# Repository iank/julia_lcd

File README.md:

# julia_lcd

TFT LCD panel, capacitive touch controller, Xilinx Cyclone IV FPGA, SDR SDRAM

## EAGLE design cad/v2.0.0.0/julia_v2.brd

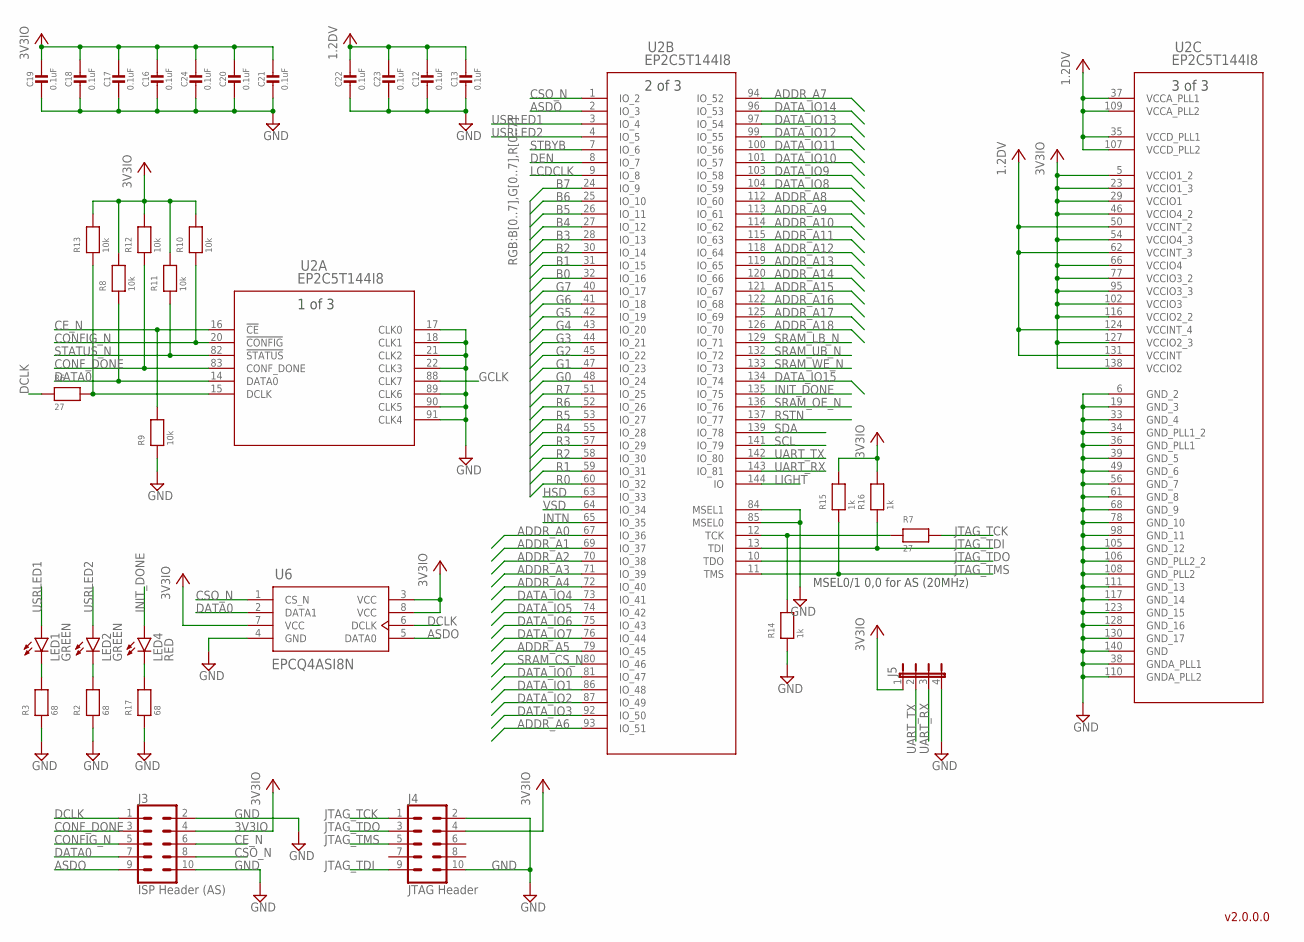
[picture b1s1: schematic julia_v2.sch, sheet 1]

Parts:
C12, C13, C16, C17, C18, C19, C20, C21, C22, C23, C24: 0.1uF; 0805; MPN 0805ZD104KAT2A
J3: ISP Header (AS); 2X5-SHROUDED; MPN SBH11-PBPC-D05-ST-BK
J4: JTAG Header; 2X5-SHROUDED; MPN SBH11-PBPC-D05-ST-BK
J5: JP4E; JP4
LED1, LED2: GREEN; CHIPLED_0805; MPN ML-LXT0805IW-TR
LED4: RED; CHIPLED_0805; MPN SML-LXT0805IW-TR
R2, R3, R17: 68; 0805; MPN RC0805FR-0768RL
R6, R7: 27; 0805; MPN RC0805JR-0727RL
R8, R9, R10, R11, R12, R13: 10k; 0805; MPN RC0805FR-0710KL
R14, R15, R16: 1k; 0805; MPN RC0805FR-071KL
U2: EP2C5T144I8; 144-TQFP_ALR; MPN EP2C5T144I8
U6: EPCQ4ASI8N; 8SOIC

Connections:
1.2DV: C12.1, C13.1, C22.1, C23.1, U2.35 (VCCD_PLL1), U2.37 (VCCA_PLL1), U2.50 (VCCINT_2), U2.62 (VCCINT_3), U2.107 (VCCD_PLL2), U2.109 (VCCA_PLL2), U2.124 (VCCINT_4), U2.131 (VCCINT); also elsewhere on the board
3V3IO: C16.1, C17.1, C18.1, C19.1, C20.1, C21.1, C24.1, J3.4, J4.4, J5.1, R8.2, R10.2, R11.2, R12.2, R13.2, R15.2, R16.2, U2.5 (VCCIO1_2), U2.23 (VCCIO1_3), U2.29 (VCCIO1), U2.46 (VCCIO4_2), U2.54 (VCCIO4_3), U2.66 (VCCIO4), U2.77 (VCCIO3_2), U2.95 (VCCIO3_3), U2.102 (VCCIO3), U2.116 (VCCIO2_2), U2.127 (VCCIO2_3), U2.138 (VCCIO2), U6.3 (VCC), U6.7 (VCC), U6.8 (VCC); also elsewhere on the board
ADDR_A0: U2.67 (IO_36); also elsewhere on the board
ADDR_A1: U2.69 (IO_37); also elsewhere on the board
ADDR_A2: U2.70 (IO_38); also elsewhere on the board
ADDR_A3: U2.71 (IO_39); also elsewhere on the board
ADDR_A4: U2.72 (IO_40); also elsewhere on the board
ADDR_A5: U2.79 (IO_45); also elsewhere on the board
ADDR_A6: U2.93 (IO_51); also elsewhere on the board
ADDR_A7: U2.94 (IO_52); also elsewhere on the board
ADDR_A8: U2.112 (IO_60); also elsewhere on the board
ADDR_A9: U2.113 (IO_61); also elsewhere on the board
ADDR_A10: U2.114 (IO_62); also elsewhere on the board
ADDR_A11: U2.115 (IO_63); also elsewhere on the board
ADDR_A12: U2.118 (IO_64); also elsewhere on the board
ADDR_A13: U2.119 (IO_65); also elsewhere on the board
ADDR_A14: U2.120 (IO_66); also elsewhere on the board
ADDR_A15: U2.121 (IO_67); also elsewhere on the board
ADDR_A16: U2.122 (IO_68); also elsewhere on the board
ADDR_A17: U2.125 (IO_69); also elsewhere on the board
ADDR_A18: U2.126 (IO_70); also elsewhere on the board
ASDO: J3.9, U2.2 (IO_3), U6.5 (DATA0)
B0: U2.32 (IO_16); also elsewhere on the board
B1: U2.31 (IO_15); also elsewhere on the board
B2: U2.30 (IO_14); also elsewhere on the board
B3: U2.28 (IO_13); also elsewhere on the board
B4: U2.27 (IO_12); also elsewhere on the board
B5: U2.26 (IO_11); also elsewhere on the board
B6: U2.25 (IO_10); also elsewhere on the board
B7: U2.24 (IO_9); also elsewhere on the board
CE_N: J3.6, R9.2, U2.16 (!CE)
CONFIG_N: J3.5, R10.1, U2.20 (!CONFIG)
CONF_DONE: J3.3, R12.1, U2.83 (CONF_DONE)
CSO_N: J3.8, U2.1 (IO_2), U6.1 (CS_N)
DATA0: J3.7, R8.1, U2.14 (DATA0), U6.2 (DATA1)
DATA_IO0: U2.81 (IO_47); also elsewhere on the board
DATA_IO1: U2.86 (IO_48); also elsewhere on the board
DATA_IO2: U2.87 (IO_49); also elsewhere on the board
DATA_IO3: U2.92 (IO_50); also elsewhere on the board
DATA_IO4: U2.73 (IO_41); also elsewhere on the board
DATA_IO5: U2.74 (IO_42); also elsewhere on the board
DATA_IO6: U2.75 (IO_43); also elsewhere on the board
DATA_IO7: U2.76 (IO_44); also elsewhere on the board
DATA_IO8: U2.104 (IO_59); also elsewhere on the board
DATA_IO9: U2.103 (IO_58); also elsewhere on the board
DATA_IO10: U2.101 (IO_57); also elsewhere on the board
DATA_IO11: U2.100 (IO_56); also elsewhere on the board
DATA_IO12: U2.99 (IO_55); also elsewhere on the board
DATA_IO13: U2.97 (IO_54); also elsewhere on the board
DATA_IO14: U2.96 (IO_53); also elsewhere on the board
DATA_IO15: U2.134 (IO_74); also elsewhere on the board
DCLK: J3.1, R6.1, U6.6 (DCLK)
DEN: U2.8 (IO_7); also elsewhere on the board
G0: U2.48 (IO_24); also elsewhere on the board
G1: U2.47 (IO_23); also elsewhere on the board
G2: U2.45 (IO_22); also elsewhere on the board
G3: U2.44 (IO_21); also elsewhere on the board
G4: U2.43 (IO_20); also elsewhere on the board
G5: U2.42 (IO_19); also elsewhere on the board
G6: U2.41 (IO_18); also elsewhere on the board
G7: U2.40 (IO_17); also elsewhere on the board
GCLK: U2.88 (CLK7); also elsewhere on the board
GND: C12.2, C13.2, C16.2, C17.2, C18.2, C19.2, C20.2, C21.2, C22.2, C23.2, C24.2, J3.2, J3.10, J4.2, J4.10, J5.4, R2.1, R3.1, R9.1, R14.1, R17.1, U2.6 (GND_2), U2.17 (CLK0), U2.18 (CLK1), U2.19 (GND_3), U2.21 (CLK2), U2.22 (CLK3), U2.33 (GND_4), U2.34 (GND_PLL1_2), U2.36 (GND_PLL1), U2.38 (GNDA_PLL1), U2.39 (GND_5), U2.49 (GND_6), U2.56 (GND_7), U2.61 (GND_8), U2.68 (GND_9), U2.78 (GND_10), U2.84 (MSEL1), U2.85 (MSEL0), U2.89 (CLK6), U2.90 (CLK5), U2.91 (CLK4), U2.98 (GND_11), U2.105 (GND_12), U2.106 (GND_PLL2_2), U2.108 (GND_PLL2), U2.110 (GNDA_PLL2), U2.111 (GND_13), U2.117 (GND_14), U2.123 (GND_15), U2.128 (GND_16), U2.130 (GND_17), U2.140 (GND), U6.4 (GND); also elsewhere on the board
HSD: U2.63 (IO_33); also elsewhere on the board
INIT_DONE: LED4.A, U2.135 (IO_75)
INTN: U2.65 (IO_35); also elsewhere on the board
JTAG_TCK: J4.1, R7.2
JTAG_TDI: J4.9, R16.1, U2.13 (TDI)
JTAG_TDO: J4.3, U2.10 (TDO)
JTAG_TMS: J4.5, R15.1, U2.11 (TMS)
LCDCLK: U2.9 (IO_8); also elsewhere on the board
LIGHT: U2.144 (IO); also elsewhere on the board
unnamed: R6.2, R13.1, U2.15 (DCLK)
unnamed: LED1.C, R3.2
unnamed: R7.1, R14.2, U2.12 (TCK)
unnamed: LED4.C, R17.2
unnamed: LED2.C, R2.2
R0: U2.60 (IO_32); also elsewhere on the board
R1: U2.59 (IO_31); also elsewhere on the board
R2: U2.58 (IO_30); also elsewhere on the board
R3: U2.57 (IO_29); also elsewhere on the board
R4: U2.55 (IO_28); also elsewhere on the board
R5: U2.53 (IO_27); also elsewhere on the board
R6: U2.52 (IO_26); also elsewhere on the board
R7: U2.51 (IO_25); also elsewhere on the board
RSTN: U2.137 (IO_77); also elsewhere on the board
SCL: U2.141 (IO_79); also elsewhere on the board
SDA: U2.139 (IO_78); also elsewhere on the board
SRAM_CS_N: U2.80 (IO_46); also elsewhere on the board
SRAM_LB_N: U2.129 (IO_71); also elsewhere on the board
SRAM_OE_N: U2.136 (IO_76); also elsewhere on the board
SRAM_UB_N: U2.132 (IO_72); also elsewhere on the board
SRAM_WE_N: U2.133 (IO_73); also elsewhere on the board
STATUS_N: R11.1, U2.82 (!STATUS); also elsewhere on the board
STBYB: U2.7 (IO_6); also elsewhere on the board
UART_RX: J5.3, U2.143 (IO_81)
UART_TX: J5.2, U2.142 (IO_80)
USRLED1: LED1.A, U2.3 (IO_4)
USRLED2: LED2.A, U2.4 (IO_5)
VSD: U2.64 (IO_34); also elsewhere on the board

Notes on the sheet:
MSEL0/1 0,0 for AS (20MHz)
v2.0.0.0

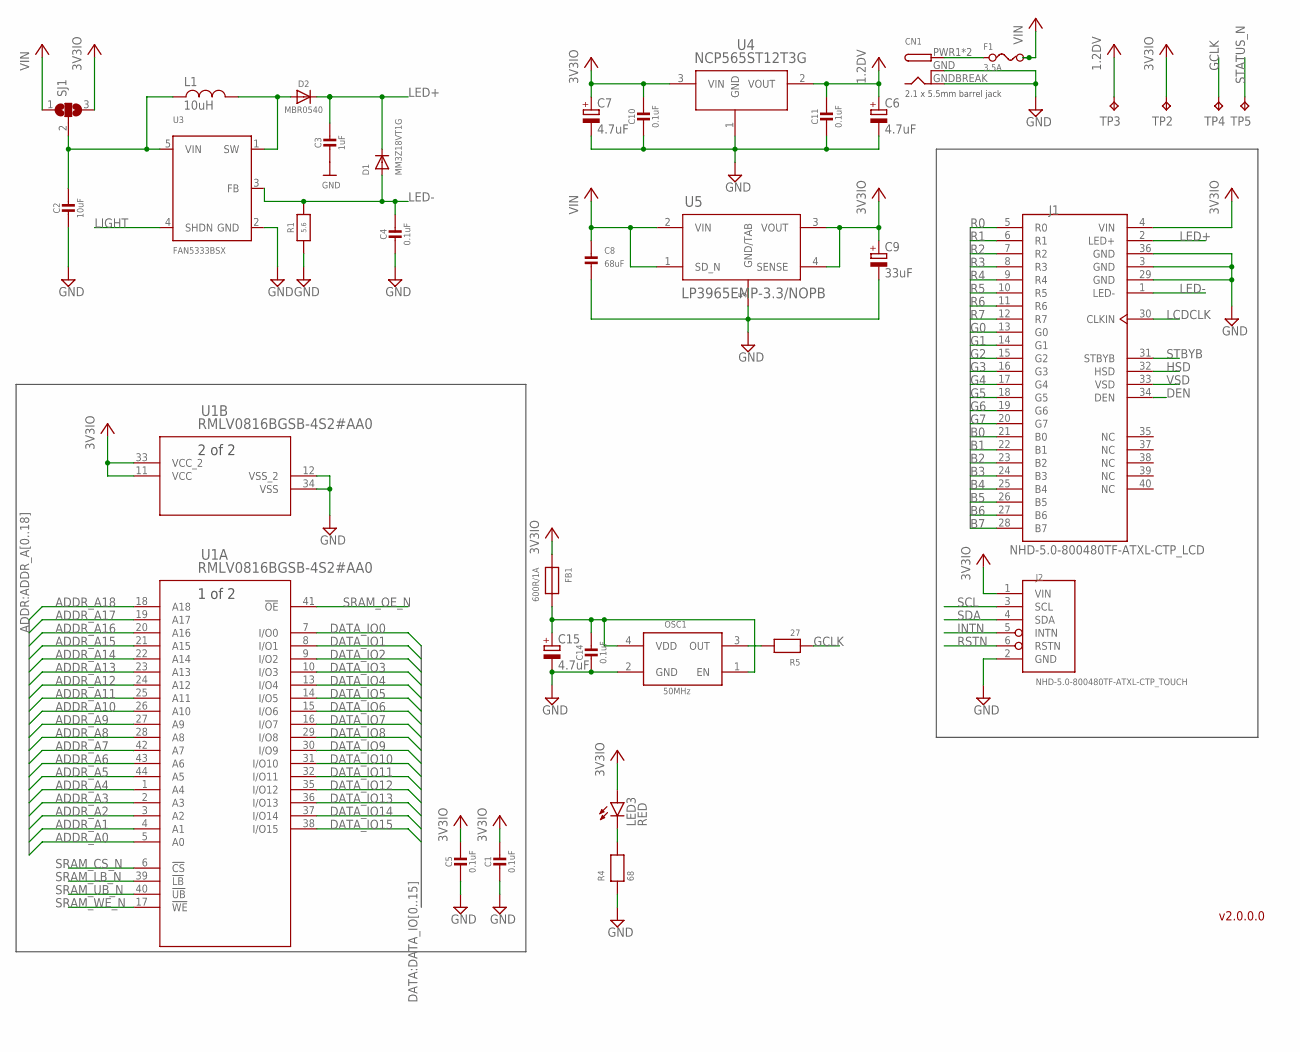
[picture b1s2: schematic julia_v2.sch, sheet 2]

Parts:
C1, C4, C5, C10, C11, C14: 0.1uF; 0805; MPN 0805ZD104KAT2A
C2: 10uF; 0805; MPN CL21A106KPFNNNG
C3: 1uF; 0805; MPN CL21A105KACLNNC
C6, C7, C15: 4.7uF; CPOL0805; MPN F920J475MPA
C8: 68uF; 1206; MPN C3216X5R1A686M160AC
C9: 33uF; CPOL0805; MPN TLJP336M010R3500
CN1: DCBARRELSMT; DCJACK_2MM_SMT
D1: MM3Z18VT1G; SOD-323; MPN MM3Z18VT1G
D2: MBR0540; SOD-123; MPN MBR0540
F1: 3.5A; 1206
FB1: 600R/1A; 0603; MPN MI0603J601R-10
J1: NHD-5.0-800480TF-ATXL-CTP_LCD; 54132-4097; MPN 54104-4031
J2: NHD-5.0-800480TF-ATXL-CTP_TOUCH; 52271-0679; MPN 52271-0679
L1: 10uH; SPM10040T-100M-HZ
LED3: RED; CHIPLED_0805; MPN SML-LXT0805IW-TR
OSC1: 50MHz; CRYSTALASV
R1: 5.6; 0805; MPN RC0805FR-075R6L
R4: 68; 0805; MPN RC0805FR-0768RL
R5: 27; 0805; MPN RC0805JR-0727RL
SJ1: SJ2WW; SJ_2W
TP2, TP3, TP4, TP5: TPB1,27; B1,27
U1: RMLV0816BGSB-4S2#AA0; PTSB0044GG-A_REN
U3: FAN5333BSX; SOT23-5@1; MPN FAN5333BSX
U4: NCP565ST12T3G; SOT223-3_ONS
U5: LP3965EMP-3.3/NOPB; NDC0005A

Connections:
1.2DV: C6.1 (+), C11.1, TP3.TP, U4.2 (VOUT); also elsewhere on the board
3V3IO: C1.1, C5.1, C7.1 (+), C9.1 (+), C10.1, FB1.1, J1.4 (VIN), J2.1 (VIN), LED3.A, SJ1.3, TP2.TP, U1.11 (VCC), U1.33 (VCC_2), U4.3 (VIN), U5.3 (VOUT), U5.4 (SENSE); also elsewhere on the board
ADDR_A0: U1.5 (A0); also elsewhere on the board
ADDR_A1: U1.4 (A1); also elsewhere on the board
ADDR_A2: U1.3 (A2); also elsewhere on the board
ADDR_A3: U1.2 (A3); also elsewhere on the board
ADDR_A4: U1.1 (A4); also elsewhere on the board
ADDR_A5: U1.44 (A5); also elsewhere on the board
ADDR_A6: U1.43 (A6); also elsewhere on the board
ADDR_A7: U1.42 (A7); also elsewhere on the board
ADDR_A8: U1.28 (A8); also elsewhere on the board
ADDR_A9: U1.27 (A9); also elsewhere on the board
ADDR_A10: U1.26 (A10); also elsewhere on the board
ADDR_A11: U1.25 (A11); also elsewhere on the board
ADDR_A12: U1.24 (A12); also elsewhere on the board
ADDR_A13: U1.23 (A13); also elsewhere on the board
ADDR_A14: U1.22 (A14); also elsewhere on the board
ADDR_A15: U1.21 (A15); also elsewhere on the board
ADDR_A16: U1.20 (A16); also elsewhere on the board
ADDR_A17: U1.19 (A17); also elsewhere on the board
ADDR_A18: U1.18 (A18); also elsewhere on the board
B0: J1.21 (B0); also elsewhere on the board
B1: J1.22 (B1); also elsewhere on the board
B2: J1.23 (B2); also elsewhere on the board
B3: J1.24 (B3); also elsewhere on the board
B4: J1.25 (B4); also elsewhere on the board
B5: J1.26 (B5); also elsewhere on the board
B6: J1.27 (B6); also elsewhere on the board
B7: J1.28 (B7); also elsewhere on the board
DATA_IO0: U1.7 (I/O0); also elsewhere on the board
DATA_IO1: U1.8 (I/O1); also elsewhere on the board
DATA_IO2: U1.9 (I/O2); also elsewhere on the board
DATA_IO3: U1.10 (I/O3); also elsewhere on the board
DATA_IO4: U1.13 (I/O4); also elsewhere on the board
DATA_IO5: U1.14 (I/O5); also elsewhere on the board
DATA_IO6: U1.15 (I/O6); also elsewhere on the board
DATA_IO7: U1.16 (I/O7); also elsewhere on the board
DATA_IO8: U1.29 (I/O8); also elsewhere on the board
DATA_IO9: U1.30 (I/O9); also elsewhere on the board
DATA_IO10: U1.31 (I/O10); also elsewhere on the board
DATA_IO11: U1.32 (I/O11); also elsewhere on the board
DATA_IO12: U1.35 (I/O12); also elsewhere on the board
DATA_IO13: U1.36 (I/O13); also elsewhere on the board
DATA_IO14: U1.37 (I/O14); also elsewhere on the board
DATA_IO15: U1.38 (I/O15); also elsewhere on the board
DEN: J1.34 (DEN); also elsewhere on the board
F_SW: D2.A, L1.1, U3.1 (SW)
F_VIN: C2.1, L1.2, SJ1.2, U3.5 (VIN)
G0: J1.13 (G0); also elsewhere on the board
G1: J1.14 (G1); also elsewhere on the board
G2: J1.15 (G2); also elsewhere on the board
G3: J1.16 (G3); also elsewhere on the board
G4: J1.17 (G4); also elsewhere on the board
G5: J1.18 (G5); also elsewhere on the board
G6: J1.19 (G6); also elsewhere on the board
G7: J1.20 (G7); also elsewhere on the board
GCLK: R5.1, TP4.TP; also elsewhere on the board
GND: C1.2, C2.2, C3.2, C4.2, C5.2, C6.2 (-), C7.2 (-), C8.2, C9.2 (-), C10.2, C11.2, C14.2, C15.2 (-), CN1.GND, CN1.GNDBREAK, J1.3 (GND), J1.29 (GND), J1.36 (GND), J2.2 (GND), OSC1.2 (GND), R1.1, R4.1, U1.12 (VSS_2), U1.34 (VSS), U3.2 (GND), U4.1 (GND), U5.5 (GND/TAB); also elsewhere on the board
HSD: J1.32 (HSD); also elsewhere on the board
INTN: J2.5 (INTN); also elsewhere on the board
LCDCLK: J1.30 (CLKIN); also elsewhere on the board
LED+: C3.1, D1.1 (C), D2.C, J1.2 (LED+)
LED-: C4.1, D1.2 (A), J1.1 (LED-), R1.2, U3.3 (FB)
LIGHT: U3.4 (SHDN); also elsewhere on the board
unnamed: CN1.PWR1 (PWR), CN1.PWR2 (PWR), F1.1
unnamed: LED3.C, R4.2
OSC_V: C14.1, C15.1 (+), FB1.2, OSC1.1 (EN), OSC1.4 (VDD)
R0: J1.5 (R0); also elsewhere on the board
R1: J1.6 (R1); also elsewhere on the board
R2: J1.7 (R2); also elsewhere on the board
R3: J1.8 (R3); also elsewhere on the board
R4: J1.9 (R4); also elsewhere on the board
R5: J1.10 (R5); also elsewhere on the board
R6: J1.11 (R6); also elsewhere on the board
R7: J1.12 (R7); also elsewhere on the board
RSTN: J2.6 (RSTN); also elsewhere on the board
SCL: J2.3 (SCL); also elsewhere on the board
SDA: J2.4 (SDA); also elsewhere on the board
SRAM_CS_N: U1.6 (!CS); also elsewhere on the board
SRAM_LB_N: U1.39 (!LB); also elsewhere on the board
SRAM_OE_N: U1.41 (!OE); also elsewhere on the board
SRAM_UB_N: U1.40 (!UB); also elsewhere on the board
SRAM_WE_N: U1.17 (!WE); also elsewhere on the board
STATUS_N: TP5.TP; also elsewhere on the board
STBYB: J1.31 (STBYB); also elsewhere on the board
VIN: C8.1, F1.2, SJ1.1, U5.1 (SD_N), U5.2 (VIN)
VSD: J1.33 (VSD); also elsewhere on the board
_GCLK: OSC1.3 (OUT), R5.2

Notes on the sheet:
2.1 x 5.5mm barrel jack
v2.0.0.0

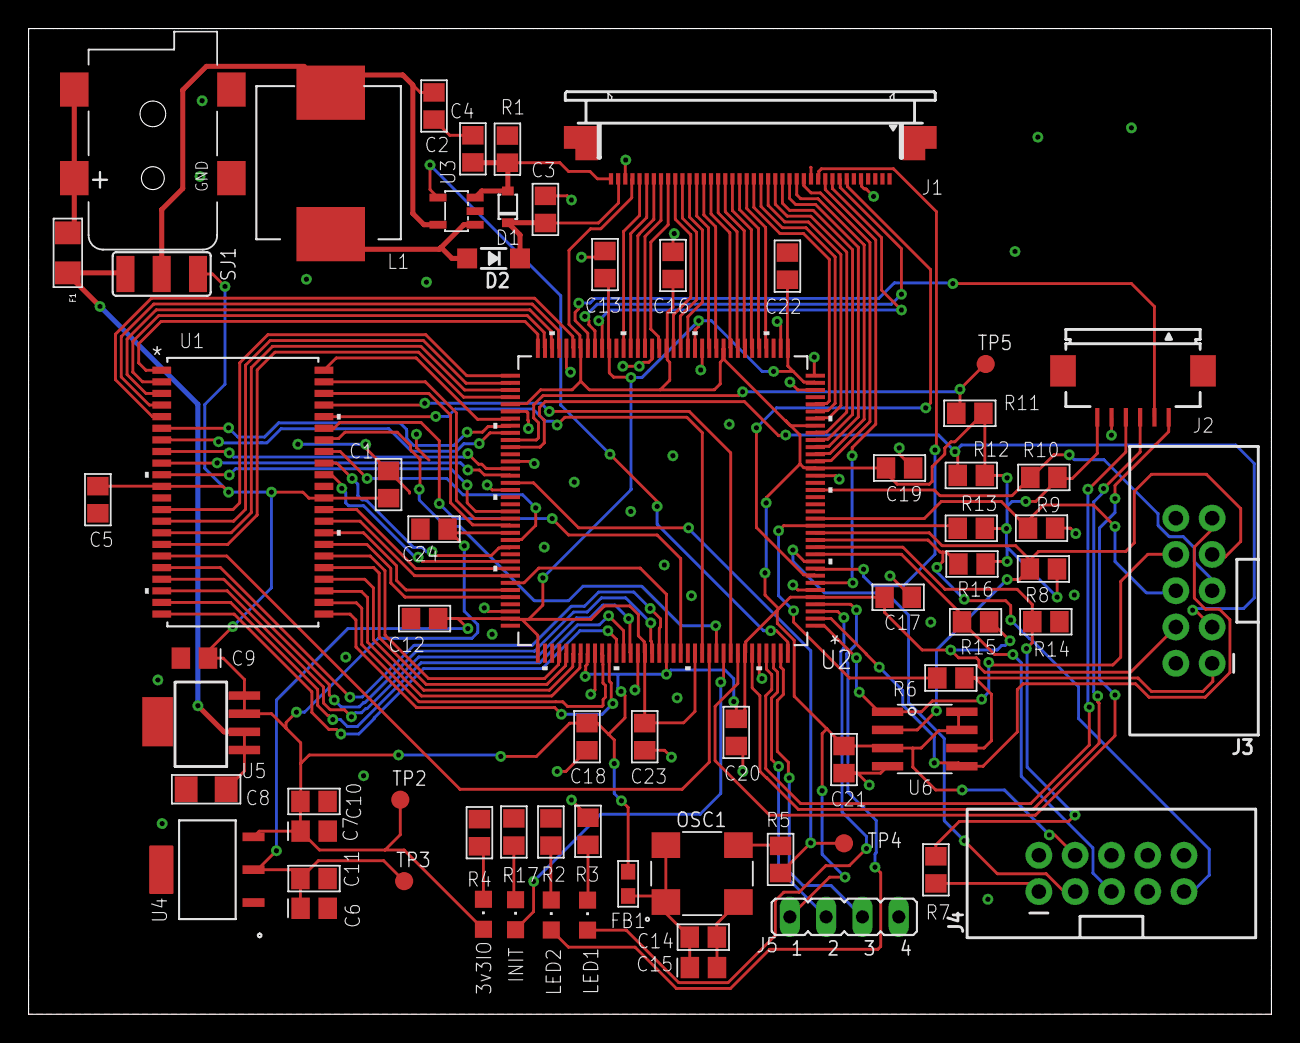
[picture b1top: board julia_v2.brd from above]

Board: 2 copper layers, 87.0 x 69.0 mm, 68 parts (0 on the bottom side), 109 nets.

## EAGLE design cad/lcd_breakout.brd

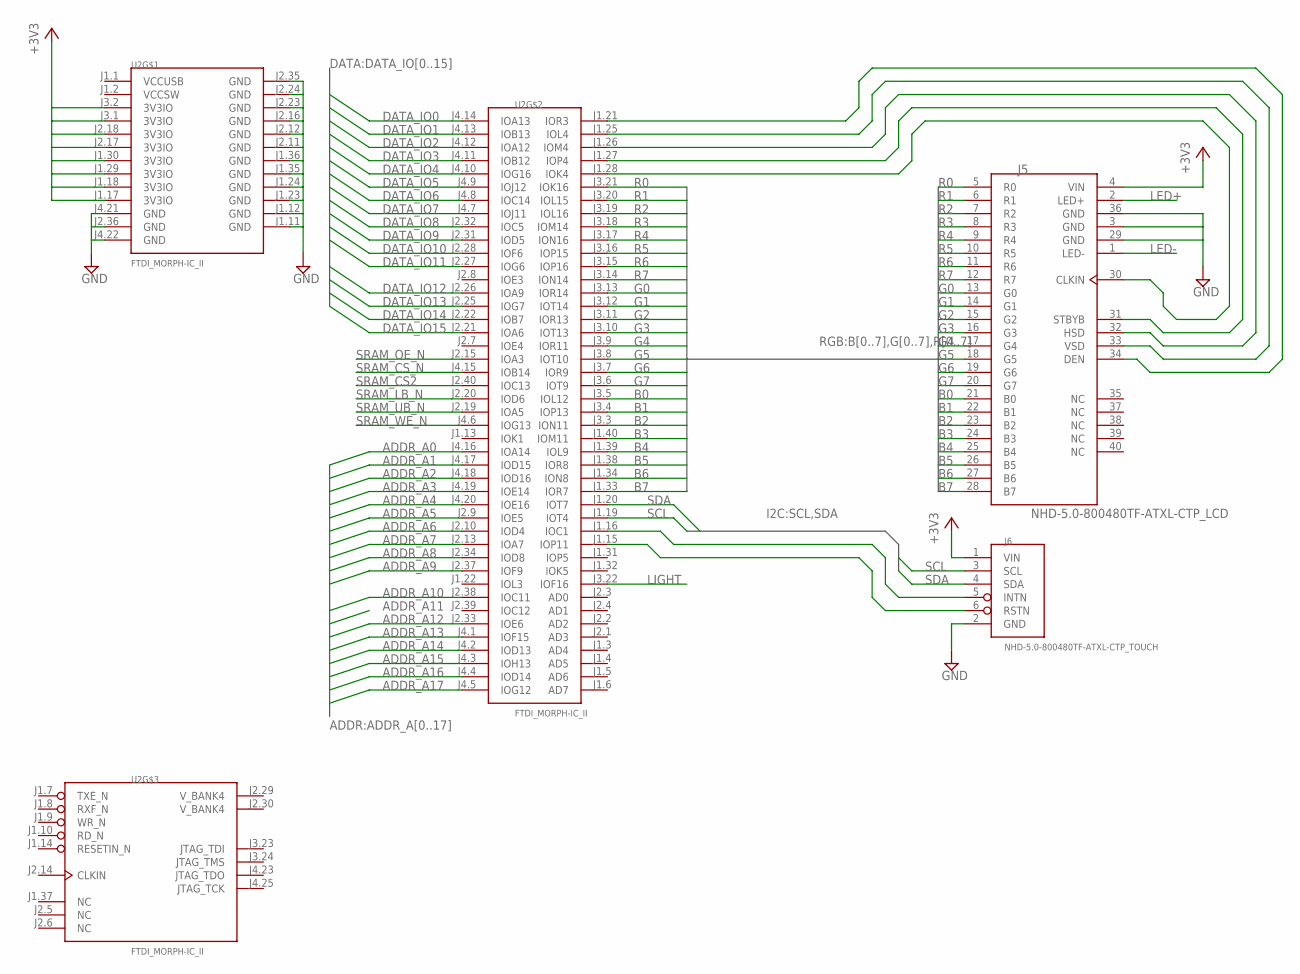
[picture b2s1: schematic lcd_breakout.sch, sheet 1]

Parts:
J5: NHD-5.0-800480TF-ATXL-CTP_LCD; 54132-4097; MPN 54104-4031
J6: NHD-5.0-800480TF-ATXL-CTP_TOUCH; 52271-0679; MPN 52271-0679
U2: FTDI_MORPH-IC_II; MORPH-IC-II; MPN 2x NPPC202KFMS-RC, 2x NPPC122KFMS-RC

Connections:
+3V3: J5.4 (VIN), J6.1 (VIN), U2.J1.17 (3V3IO), U2.J1.18 (3V3IO), U2.J1.29 (3V3IO), U2.J1.30 (3V3IO), U2.J2.17 (3V3IO), U2.J2.18 (3V3IO), U2.J3.1 (3V3IO), U2.J3.2 (3V3IO); also elsewhere on the board
ADDR_A0: U2.J4.16 (IOA14); also elsewhere on the board
ADDR_A1: U2.J4.17 (IOD15); also elsewhere on the board
ADDR_A2: U2.J4.18 (IOD16); also elsewhere on the board
ADDR_A3: U2.J4.19 (IOE14); also elsewhere on the board
ADDR_A4: U2.J4.20 (IOE16); also elsewhere on the board
ADDR_A5: U2.J2.9 (IOE5); also elsewhere on the board
ADDR_A6: U2.J2.10 (IOD4); also elsewhere on the board
ADDR_A7: U2.J2.13 (IOA7); also elsewhere on the board
ADDR_A8: U2.J2.34 (IOD8); also elsewhere on the board
ADDR_A9: U2.J2.37 (IOF9); also elsewhere on the board
ADDR_A10: U2.J2.38 (IOC11); also elsewhere on the board
ADDR_A12: U2.J2.33 (IOE6); also elsewhere on the board
ADDR_A13: U2.J4.1 (IOF15); also elsewhere on the board
ADDR_A14: U2.J4.2 (IOD13); also elsewhere on the board
ADDR_A15: U2.J4.3 (IOH13); also elsewhere on the board
ADDR_A16: U2.J4.4 (IOD14); also elsewhere on the board
ADDR_A17: U2.J4.5 (IOG12); also elsewhere on the board
B0: J5.21 (B0), U2.J3.5 (IOL12)
B1: J5.22 (B1), U2.J3.4 (IOP13)
B2: J5.23 (B2), U2.J3.3 (ION11)
B3: J5.24 (B3), U2.J1.40 (IOM11)
B4: J5.25 (B4), U2.J1.39 (IOL9)
B5: J5.26 (B5), U2.J1.38 (IOR8)
B6: J5.27 (B6), U2.J1.34 (ION8)
B7: J5.28 (B7), U2.J1.33 (IOR7)
CLKIN: J5.30 (CLKIN), U2.J1.28 (IOK4)
DATA_IO0: U2.J4.14 (IOA13); also elsewhere on the board
DATA_IO1: U2.J4.13 (IOB13); also elsewhere on the board
DATA_IO2: U2.J4.12 (IOA12); also elsewhere on the board
DATA_IO3: U2.J4.11 (IOB12); also elsewhere on the board
DATA_IO4: U2.J4.10 (IOG16); also elsewhere on the board
DATA_IO5: U2.J4.9 (IOJ12); also elsewhere on the board
DATA_IO6: U2.J4.8 (IOC14); also elsewhere on the board
DATA_IO7: U2.J4.7 (IOJ11); also elsewhere on the board
DATA_IO8: U2.J2.32 (IOC5); also elsewhere on the board
DATA_IO9: U2.J2.31 (IOD5); also elsewhere on the board
DATA_IO10: U2.J2.28 (IOF6); also elsewhere on the board
DATA_IO11: U2.J2.27 (IOG6); also elsewhere on the board
DATA_IO12: U2.J2.26 (IOA9); also elsewhere on the board
DATA_IO13: U2.J2.25 (IOG7); also elsewhere on the board
DATA_IO14: U2.J2.22 (IOB7); also elsewhere on the board
DATA_IO15: U2.J2.21 (IOA6); also elsewhere on the board
DEN: J5.34 (DEN), U2.J1.21 (IOR3)
G0: J5.13 (G0), U2.J3.13 (IOR14)
G1: J5.14 (G1), U2.J3.12 (IOT14)
G2: J5.15 (G2), U2.J3.11 (IOR13)
G3: J5.16 (G3), U2.J3.10 (IOT13)
G4: J5.17 (G4), U2.J3.9 (IOR11)
G5: J5.18 (G5), U2.J3.8 (IOT10)
G6: J5.19 (G6), U2.J3.7 (IOR9)
G7: J5.20 (G7), U2.J3.6 (IOT9)
GND: J5.3 (GND), J5.29 (GND), J5.36 (GND), J6.2 (GND), U2.J1.11 (GND), U2.J1.12 (GND), U2.J1.23 (GND), U2.J1.24 (GND), U2.J1.35 (GND), U2.J1.36 (GND), U2.J2.11 (GND), U2.J2.12 (GND), U2.J2.16 (GND), U2.J2.23 (GND), U2.J2.24 (GND), U2.J2.35 (GND), U2.J2.36 (GND), U2.J4.21 (GND), U2.J4.22 (GND); also elsewhere on the board
HSD: J5.32 (HSD), U2.J1.26 (IOM4)
INTN: J6.5 (INTN), U2.J1.16 (IOC1)
LED+: J5.2 (LED+); also elsewhere on the board
LED-: J5.1 (LED-); also elsewhere on the board
LIGHT: U2.J3.22 (IOF16); also elsewhere on the board
R0: J5.5 (R0), U2.J3.21 (IOK16)
R1: J5.6 (R1), U2.J3.20 (IOL15)
R2: J5.7 (R2), U2.J3.19 (IOL16)
R3: J5.8 (R3), U2.J3.18 (IOM14)
R4: J5.9 (R4), U2.J3.17 (ION16)
R5: J5.10 (R5), U2.J3.16 (IOP15)
R6: J5.11 (R6), U2.J3.15 (IOP16)
R7: J5.12 (R7), U2.J3.14 (ION14)
RSTN: J6.6 (RSTN), U2.J1.15 (IOP11)
SCL: J6.3 (SCL), U2.J1.19 (IOT4)
SDA: J6.4 (SDA), U2.J1.20 (IOT7)
SRAM_CS2: U2.J2.40 (IOC13); also elsewhere on the board
SRAM_CS_N: U2.J4.15 (IOB14); also elsewhere on the board
SRAM_LB_N: U2.J2.20 (IOD6); also elsewhere on the board
SRAM_OE_N: U2.J2.15 (IOA3); also elsewhere on the board
SRAM_UB_N: U2.J2.19 (IOA5); also elsewhere on the board
SRAM_WE_N: U2.J4.6 (IOG13); also elsewhere on the board
STBYB: J5.31 (STBYB), U2.J1.27 (IOP4)
VCCSW: U2.J1.2 (VCCSW)
VCCUSB: U2.J1.1 (VCCUSB)
VSD: J5.33 (VSD), U2.J1.25 (IOL4)

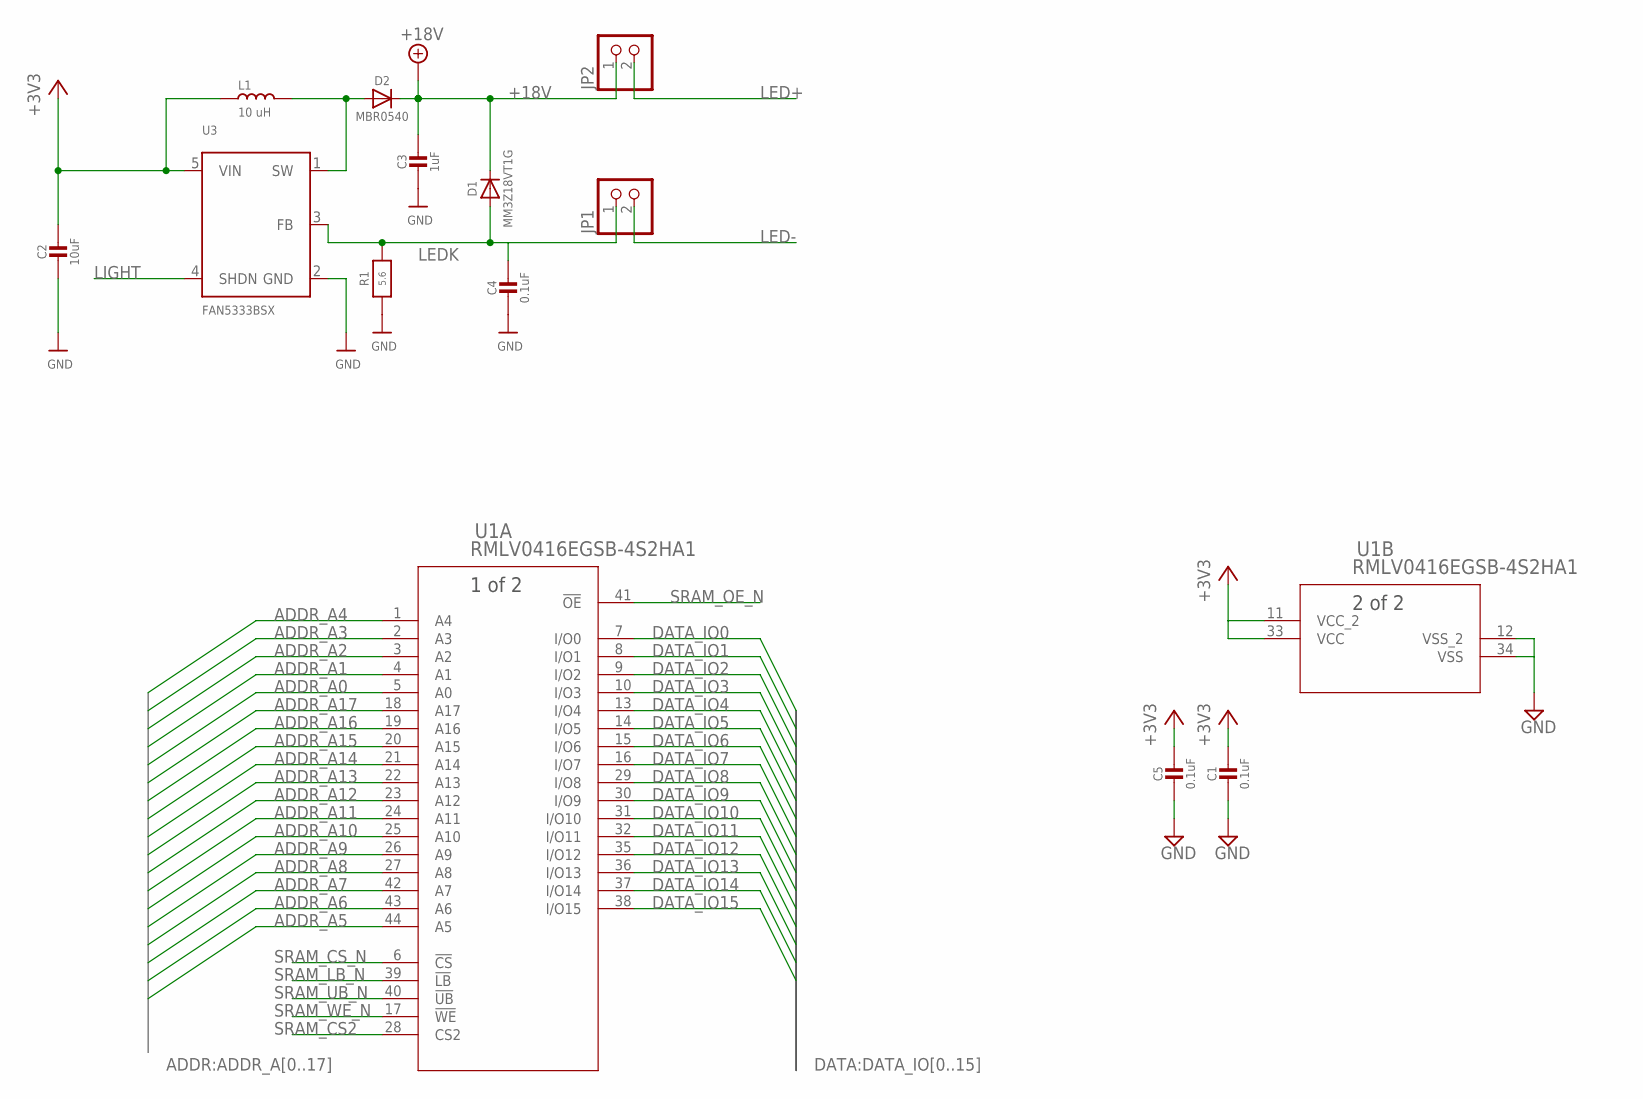
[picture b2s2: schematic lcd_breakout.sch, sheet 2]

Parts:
C1, C5: 0.1uF; _0805MP; MPN 0805ZD104KAT2A
C2: 10uF; _0805MP; MPN CL21A106KPFNNNG
C3: 1uF; 0805-NO; MPN CL21A105KACLNNC
C4: 0.1uF; 0805-NO; MPN 0805ZD104KAT2A
D1: MM3Z18VT1G; SMADIODE; MPN MM3Z18VT1G
D2: MBR0540; SOD-123; MPN MBR0540
JP1, JP2: PINHD-1X2; 1X02; MPN 4-103328-1
L1: 10 uH; IND_744314101_WRE; MPN 744314101
R1: 5.6; _0805MP; MPN RC0805FR-075R6L
U1: RMLV0416EGSB-4S2HA1; PTSB0044GG-A_REN; MPN RMLV0416EGSB-4S2#HA1
U3: FAN5333BSX; SOT23-5@1; MPN FAN5333BSX

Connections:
+3V3: C1.1, C2.1, C5.1, L1.2, U1.11 (VCC_2), U1.33 (VCC), U3.5 (VIN); also elsewhere on the board
+18V: C3.1, D1.C, D2.C, JP2.1
ADDR_A0: U1.5 (A0); also elsewhere on the board
ADDR_A1: U1.4 (A1); also elsewhere on the board
ADDR_A2: U1.3 (A2); also elsewhere on the board
ADDR_A3: U1.2 (A3); also elsewhere on the board
ADDR_A4: U1.1 (A4); also elsewhere on the board
ADDR_A5: U1.44 (A5); also elsewhere on the board
ADDR_A6: U1.43 (A6); also elsewhere on the board
ADDR_A7: U1.42 (A7); also elsewhere on the board
ADDR_A8: U1.27 (A8); also elsewhere on the board
ADDR_A9: U1.26 (A9); also elsewhere on the board
ADDR_A10: U1.25 (A10); also elsewhere on the board
ADDR_A11: U1.24 (A11)
ADDR_A12: U1.23 (A12); also elsewhere on the board
ADDR_A13: U1.22 (A13); also elsewhere on the board
ADDR_A14: U1.21 (A14); also elsewhere on the board
ADDR_A15: U1.20 (A15); also elsewhere on the board
ADDR_A16: U1.19 (A16); also elsewhere on the board
ADDR_A17: U1.18 (A17); also elsewhere on the board
DATA_IO0: U1.7 (I/O0); also elsewhere on the board
DATA_IO1: U1.8 (I/O1); also elsewhere on the board
DATA_IO2: U1.9 (I/O2); also elsewhere on the board
DATA_IO3: U1.10 (I/O3); also elsewhere on the board
DATA_IO4: U1.13 (I/O4); also elsewhere on the board
DATA_IO5: U1.14 (I/O5); also elsewhere on the board
DATA_IO6: U1.15 (I/O6); also elsewhere on the board
DATA_IO7: U1.16 (I/O7); also elsewhere on the board
DATA_IO8: U1.29 (I/O8); also elsewhere on the board
DATA_IO9: U1.30 (I/O9); also elsewhere on the board
DATA_IO10: U1.31 (I/O10); also elsewhere on the board
DATA_IO11: U1.32 (I/O11); also elsewhere on the board
DATA_IO12: U1.35 (I/O12); also elsewhere on the board
DATA_IO13: U1.36 (I/O13); also elsewhere on the board
DATA_IO14: U1.37 (I/O14); also elsewhere on the board
DATA_IO15: U1.38 (I/O15); also elsewhere on the board
GND: C1.2, C2.2, C3.2, C4.2, C5.2, R1.1, U1.12 (VSS_2), U1.34 (VSS), U3.2 (GND); also elsewhere on the board
LED+: JP2.2; also elsewhere on the board
LED-: JP1.2; also elsewhere on the board
LEDK: C4.1, D1.A, JP1.1, R1.2, U3.3 (FB)
LIGHT: U3.4 (SHDN); also elsewhere on the board
unnamed: D2.A, L1.1, U3.1 (SW)
SRAM_CS2: U1.28 (CS2); also elsewhere on the board
SRAM_CS_N: U1.6 (!CS); also elsewhere on the board
SRAM_LB_N: U1.39 (!LB); also elsewhere on the board
SRAM_OE_N: U1.41 (!OE); also elsewhere on the board
SRAM_UB_N: U1.40 (!UB); also elsewhere on the board
SRAM_WE_N: U1.17 (!WE); also elsewhere on the board

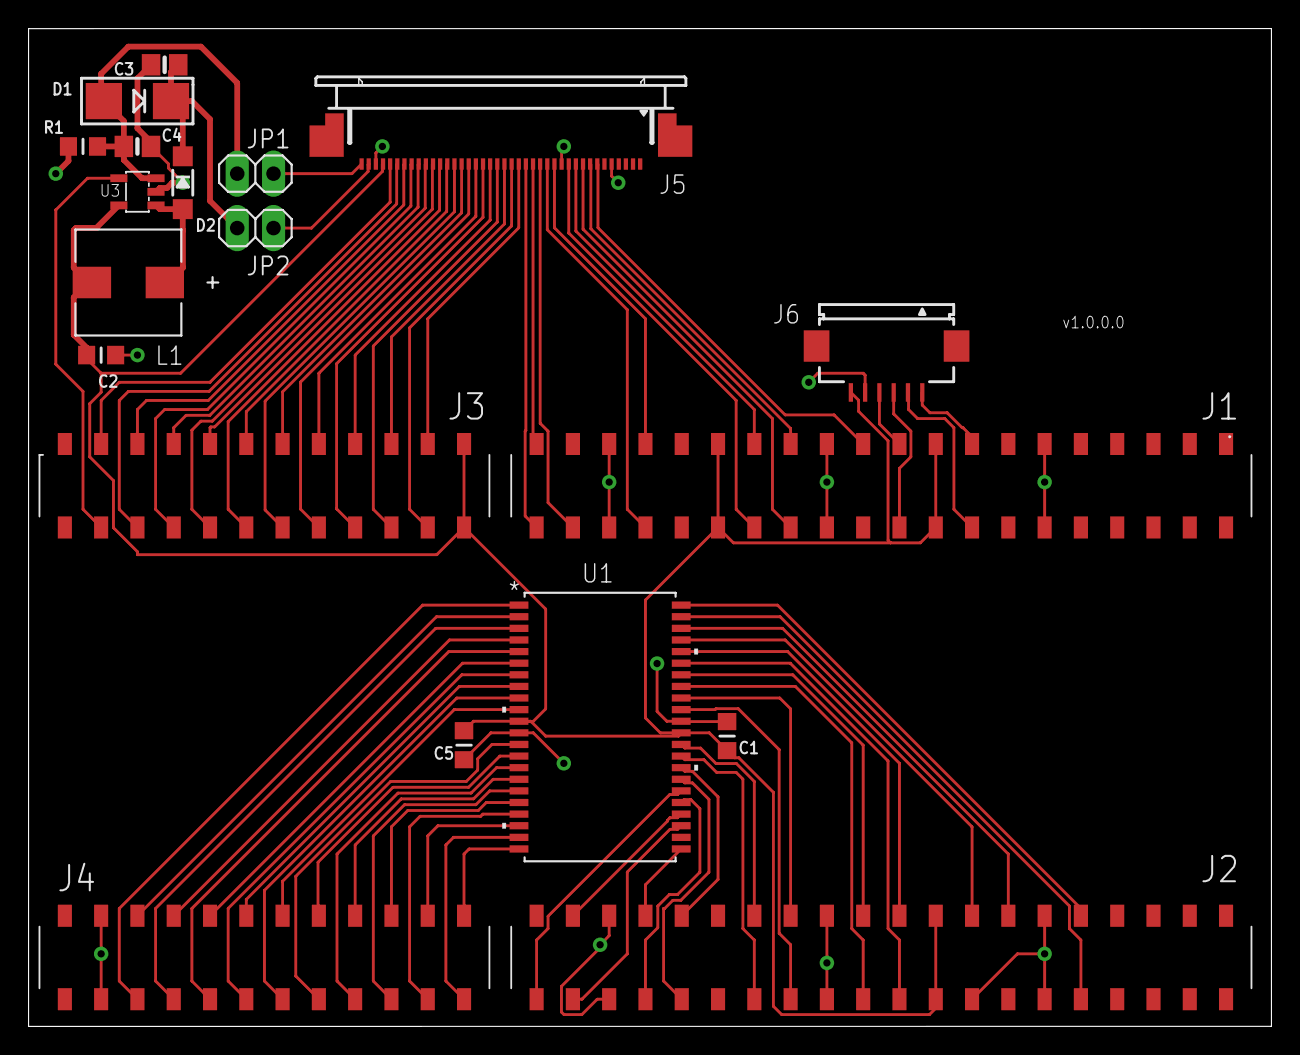
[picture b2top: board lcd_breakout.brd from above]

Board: 2 copper layers, 87.0 x 69.8 mm, 16 parts (0 on the bottom side), 80 nets.

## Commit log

2020-11-01 LCD/memory Breakout
2020-11-01 Images
2020-11-01 Board image URL
2020-11-01 Higher resolution board image
2020-11-29 Datasheets
2020-11-29 (Buggy) verilog PoC, drives screen and SRAM
2020-11-29 Fix image link in README
2020-11-29 Move v1.0.0.0 files into version directory
2020-11-29 ECNs for v1.0.0.0
2020-11-29 Fix J5 and D1 footprints in version v1.1.0.0 (not verified)
2020-12-03 v2 WiP
2020-12-04 v2 update, power and config chip
2020-12-04 Julia v2.0.0.0 schematic and BOM
2020-12-06 Julia v2.0.0.0 board
2020-12-06 v2.0.0.0 images
2020-12-06 CAM files for v2.0.0.0
2020-12-06 Update v2 status
2020-12-26 Update verilog for v2.0.0.0 board
2020-12-26 More aggressive SRAM timing; clean up top-level FSM
2021-01-01 Extremely low-precision mandelbrot (probably)
2021-01-04 v2.1.0.0 schematic
2021-01-06 Swap FAN5333BSX backlight driver for TPS61165
2021-01-08 v2.1.0.0: changed connector, ERC, annotation/footprint assignment
2021-01-09 Layout begun
2021-01-09 Layout complete(?)
2021-01-09 v2.1.0.0 gerber files
2021-01-10 Programmer breakout board for v2.1
2021-01-25 v2.1.1
2021-01-28 v2.1.1.0 BOM
2021-02-12 Clean up v2.1.1.0 FPGA sheet; update BOM
2021-02-12 Gitignore
2021-02-12 Clean up old versions, add pdf/png outputs
2021-02-12 Empty design w/ pin assignments
2021-02-13 Verilog: Video out
2021-02-13 Test fixtures for LCD and SDRAM controllers
2021-02-13 SDRAM to display FIFO (simulates but doesn't work)
2021-02-13 Fix refresh timing (still doesn't work in HW)
2021-02-14 System definition
2021-02-14 Generated BSP and project
2021-02-14 S_DQ inout -_-
2021-02-16 stable test pattern (sim/actual)
2021-02-16 rm nios
2021-02-16 Pixel fifo mixed width; Add simulation tools; verilog sim matches actual, a both a little off from JS
2021-02-17 pixel FIFO high/low thresholds
2021-02-17 Move video side of FIFO to separate file
2021-02-17 Fix tabs
2021-02-17 Rearrange some signals
2021-02-17 Sweep SDRAM init / frame reading under the rug
2021-02-17 Add SDRAM controller mux
2021-02-17 Split mem init out of frame reader
2021-02-17 Add SOF
2021-02-18 (probably working) arbitration btwn frame reader and processor
2021-02-19 processor reads/edits/writes back
2021-02-20 Update IP
2021-02-20 akxlcrakpc.ladgl.
2021-02-20 Giving up on that last thing
2021-02-20 processor checks fifo status
2021-02-20 Two processor FIFOs
2021-02-20 Test: slow down processing
2021-02-20 Fix pixel addition
2021-02-21 Clean up processor state machine
2021-02-21 processor read/write xy data
2021-02-21 Verify processor read/write xy data
2021-02-21 Update barrel jack footprint
2021-02-21 Several more 3d models
2021-02-21 Updated 3d rendering
2021-02-21 Updated 3d rendering (bottom)
2021-02-21 dual-clock FIFOs, match width.. haven't verified data
2021-02-21 Verified
2021-02-21 combine a couple signals
2021-02-21 Move math processor into module
2021-02-23 Mandelbrot. (video still misaligned)
2021-02-26 Fix FIFO overrun leading to misalignment
2021-02-26 Reasonable color map for now
2021-02-26 Increase processor clock to 20MHz
2021-02-26 Store iteration separately from pixel color
2021-02-26 MCU: blinky
2021-02-26 MCU: UART0 demo
2021-02-27 SPI flash init
2021-02-27 Move SPI flash routines out of main
2021-02-27 Refactor SPI flash init
2021-02-27 Command/response; erase chip
2021-02-27 Write and dump memory
2021-02-27 Increase SPI clock to 1.5MHz
2021-02-28 configure FPGA
2021-03-09 Generate a (particular) julia set
2021-03-09 Generate color map
2021-03-09 Draw julia or mandelbrot
2021-03-09 Overlay julia on mandelbrot
2021-03-26 Julia set constant from pixel value
2021-03-27 Touch control
2021-03-27 Clear+redraw julia when touch registers
2021-03-27 Zoom/center
2021-04-06 Color map hack for immediate feedback on touch; blank screen/backlight after couple minutes

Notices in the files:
parts and their libraries:
COPYRIGHT: Copyright (C) 2016 Accelerated Designs. All rights reserved
COPYRIGHT: Copyright (C) 2018 Accelerated Designs. All rights reserved
